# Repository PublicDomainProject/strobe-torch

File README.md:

# Strobe Torch
## Purpose
Little flashlight (or torch in UK) to calibrate the speed of a turntable with the help of a strobe disc or the strobe rings along the platter.

To use such strobe discs one needs a light source with a 50, 60 or 300 Hz strobe light. In the older days a simple light bulb with filament was enough to did the job. In the time of LEDs and compact fluorescent light sources one needs an additional helper like this to work with a strobe disc.

The needed frequency depends on your strobe disc. Most of them have at least 50 and 60 Hz in parallel (or two sides). There are "high-resolution" strobe discs that need a 300 Hz light source for calibration.

Also because this strobe torch uses a crystal oscillator it is more precise than a light bulb.

## Usage
The device is designed to be very simple to use.

There are three momentary buttons on the front. Each button represents one frequency. So simply press the 50 Hz button and you get a white light beam that flickers with 50 Hz.

When you release the button, the light goes off and the device consumes no energy.

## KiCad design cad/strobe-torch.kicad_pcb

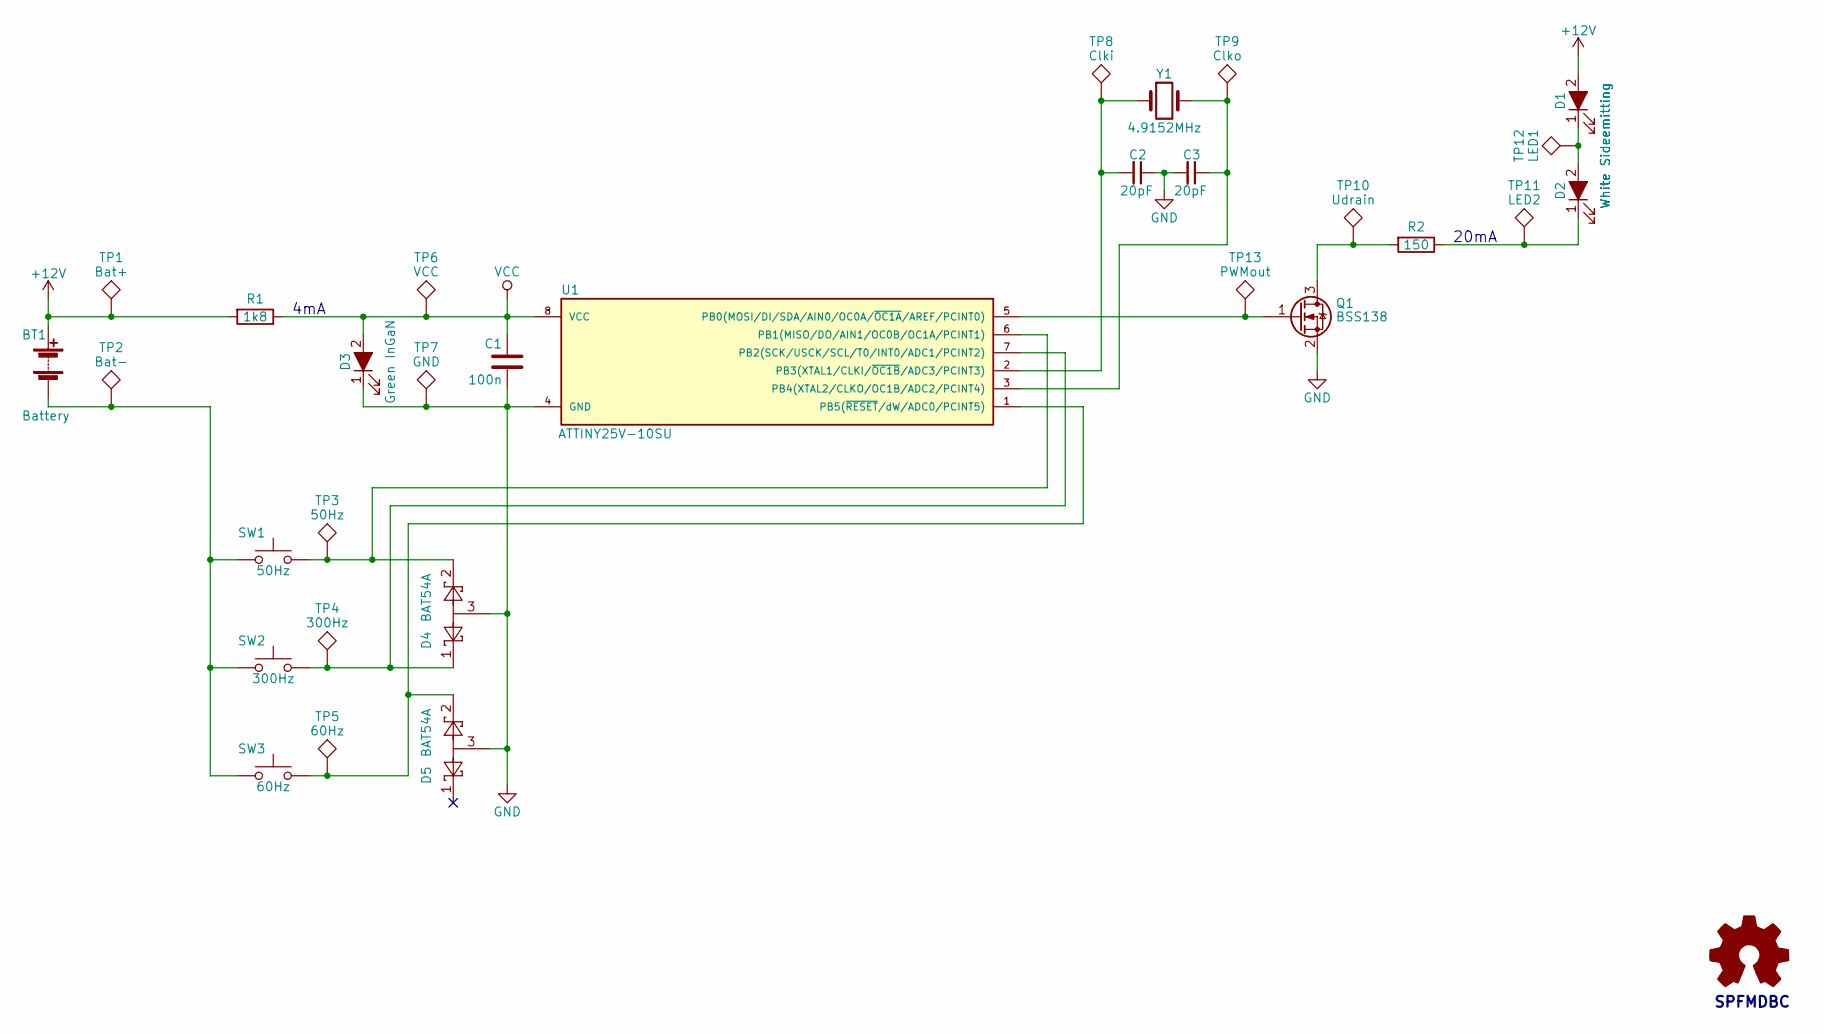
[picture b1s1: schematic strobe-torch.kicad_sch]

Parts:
BT1: Battery; Teko_1112x_battery_compartment
C1: 100n; C_0805
C2, C3: 20pF; C_0603
D1, D2: White Sideemitting; LED_215; Partnummer 215 White SMD LED 2.8*1,2*0,8mm
D3: Green InGaN; LED_0603; Partnummer 19-213/GHC-XS1T1N/3T
D4, D5: BAT54A; SOT-23
Q1: BSS138; SOT-23
R1: 1k8; R_0603
R2: 150; R_0603
SW1: 50Hz; SW_SPST_FSM6JSMA
SW2: 300Hz; SW_SPST_FSM6JSMA
SW3: 60Hz; SW_SPST_FSM6JSMA
TP1: Bat+; Measurement_Point_Round-SMD-Pad_Small
TP2: Bat-; Measurement_Point_Round-SMD-Pad_Small
TP3: 50Hz; Measurement_Point_Round-SMD-Pad_Small
TP4: 300Hz; Measurement_Point_Round-SMD-Pad_Small
TP5: 60Hz; Measurement_Point_Round-SMD-Pad_Small
TP6: VCC; Measurement_Point_Round-SMD-Pad_Small
TP7: GND; Measurement_Point_Round-SMD-Pad_Small
TP8: Clki; Measurement_Point_Round-SMD-Pad_Small
TP9: Clko; Measurement_Point_Round-SMD-Pad_Small
TP10: Udrain; Measurement_Point_Round-SMD-Pad_Small
TP11: LED2; Measurement_Point_Round-SMD-Pad_Small
TP12: LED1; Measurement_Point_Round-SMD-Pad_Small
TP13: PWMout; Measurement_Point_Round-SMD-Pad_Small
U1: ATTINY25V-10SU; SO-8_5.3x6.2mm_Pitch1.27mm
Y1: 4.9152MHz; Crystal_SMD_HC49-SD

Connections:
+12V: BT1.1 (+), D1.2 (A), R1.2, TP1.1
GND: C1.2, C2.1, C3.2, D3.1 (K), D4.3, D5.3, Q1.2 (S), TP7.1, U1.4 (GND)
unnamed: BT1.2 (-), SW1.1, SW2.1, SW3.1, TP2.1
unnamed: D1.1 (K), D2.2 (A), TP12.1
unnamed: D2.1 (K), R2.1, TP11.1
unnamed: Q1.3 (D), R2.2, TP10.1
unnamed: Q1.1 (G), TP13.1, U1.5 (PB0(MOSI/DI/SDA/AIN0/OC0A/~OC1A/AREF/PC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)
unnamed: D4.2, SW1.2, TP3.1, U1.6 (PB1(MISO/DO/AIN1/OC0B/OC1A/PCINT1))
unnamed: D4.1, SW2.2, TP4.1, U1.7 (PB2(SCK/USCK/SCL/T0/INT0/ADC1/PCINT2))
unnamed: C2.2, TP8.1, U1.2 (PB3(XTAL1/CLKI/~OC1B/ADC3/PCINT3)), Y1.1
unnamed: C3.1, TP9.1, U1.3 (PB4(XTAL2/CLKO/OC1B/ADC2/PCINT4)), Y1.2
unnamed: D5.2, SW3.2, TP5.1, U1.1 (PB5(~RESET/dW/ADC0/PCINT5))
VCC: C1.1, D3.2 (A), R1.1, TP6.1, U1.8 (VCC)

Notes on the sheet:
4mA
20mA
SPFMDBC

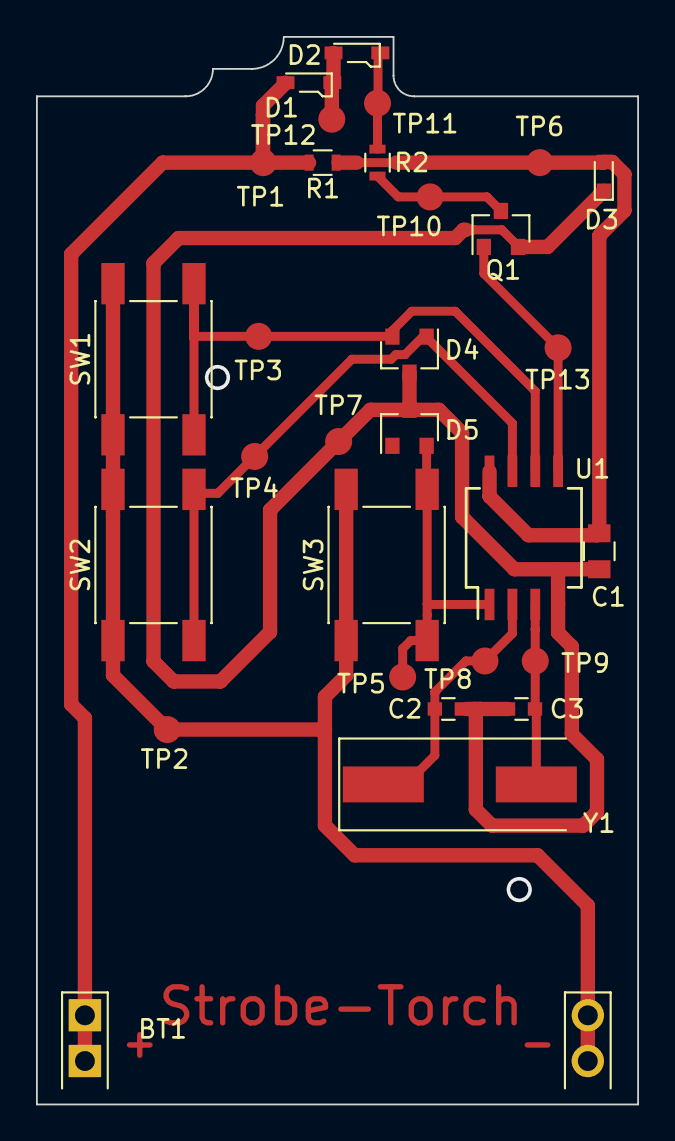
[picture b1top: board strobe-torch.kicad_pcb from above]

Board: 2 copper layers, 33.4 x 59.3 mm, 30 parts (0 on the bottom side), 13 nets.

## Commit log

2018-03-01 initial commit of the prototype design with finished schematic as intended.
2018-03-04 initial version of firmware.
    compiles, not tested on device yet.
2018-03-04 more comments
2018-03-04 More power reduction
2018-03-04 Little clean up
2018-03-04 Disabled the strict-header warnings for this project.
2018-03-13 version with ISR to toggle pwm pin direction and pull-up resistor to drive an external transistor
2018-03-13 fixed missing code to enable timer interrupt mask
2018-03-13 With the prescaler set to 256, the ISP frequency must be lower
2018-03-13 temporary disable reset as i/o. remove this commit before release.
2018-03-18 Prototype hardware changed to ATtiny25
2018-03-18 Removed unnecessary libraries. Hex file has now a reasonable size.
2018-03-21 First working version.
2018-03-26 changed pinning according to pcb layout. changed from OC1A to !OC1A (inverted) output.
2018-03-26 Updated schematic (Output MOSFET and change to Shottky diodes, changed pinning to optimize layout)
    Created footprints for Teko case and side emitting LEDs
    Initial pcb layout
2018-03-26 Sticker for the backside of the case (unbranded with space for logo) and drawing to get the LED opening milled.
2018-04-15 finalized bill of material (BOM)
2018-04-15 fixed button pressed routine. works on final circuit with three buttons and disabled reset pin.
2018-04-18 added compiled binary ready to flash onto device.
2018-04-18 Applied needed modifications after production of first samples.
2018-04-18 Adding schematic as pdf and the exported pcb files for production (Gerber, pick and place data).
2018-04-26 removed netlist because it is a generated file
2018-04-26 Created a panel with ten strobe-torch PCBs and a boarder that is wide enough to grab it in a SMD pick'n place machine. It is using v-cuts (break lines) to hold the PCBs together during production.
2020-10-11 Add manufacturing drawings for TEKO 11123 case
2020-10-11 Add panelized project (was missing in previous commits)
2020-10-11 Removed blank characters
2025-02-09 Add production files for the case sticker
2025-02-09 Change footprint of button and upgrade to KiCad 8
2025-02-09 Change button mapping. The two button case variant provides now 50 and 60 Hz instead of 50 and 300 Hz. Changed because the two button variant is easier to buy than the three button case.
    Make it work with avr-gcc 14
